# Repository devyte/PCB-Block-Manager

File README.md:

# Block Manager 
### Hardware Files For The Block Manager Board
These are the printed circuit board (PCB) files, CAD files, specification sheets and all technical drawings needed to make the DKblock Block Manager board. There are two boards that make a minimum DK system, a Block Manager PCB and a Pack Supervisor PCB (with software changes to the 20 client version provided). Note that the bill of materials (BOM) and other technical documents can be opened in [OpenOffice](https://www.openoffice.org) format and PCB files are in [EAGLE](https://www.autodesk.com/products/eagle/overview) format but they can also be opened and edited in the open source Kicad program.
One version is provided, that is Rev D which is a fully tested board.

All DKblock software and hardware is released as open source hardware (OSHW) as defined by the OSHWA: https://www.oshwa.org/definition/ and under the JSON license defined at https://www.json.org/license.html

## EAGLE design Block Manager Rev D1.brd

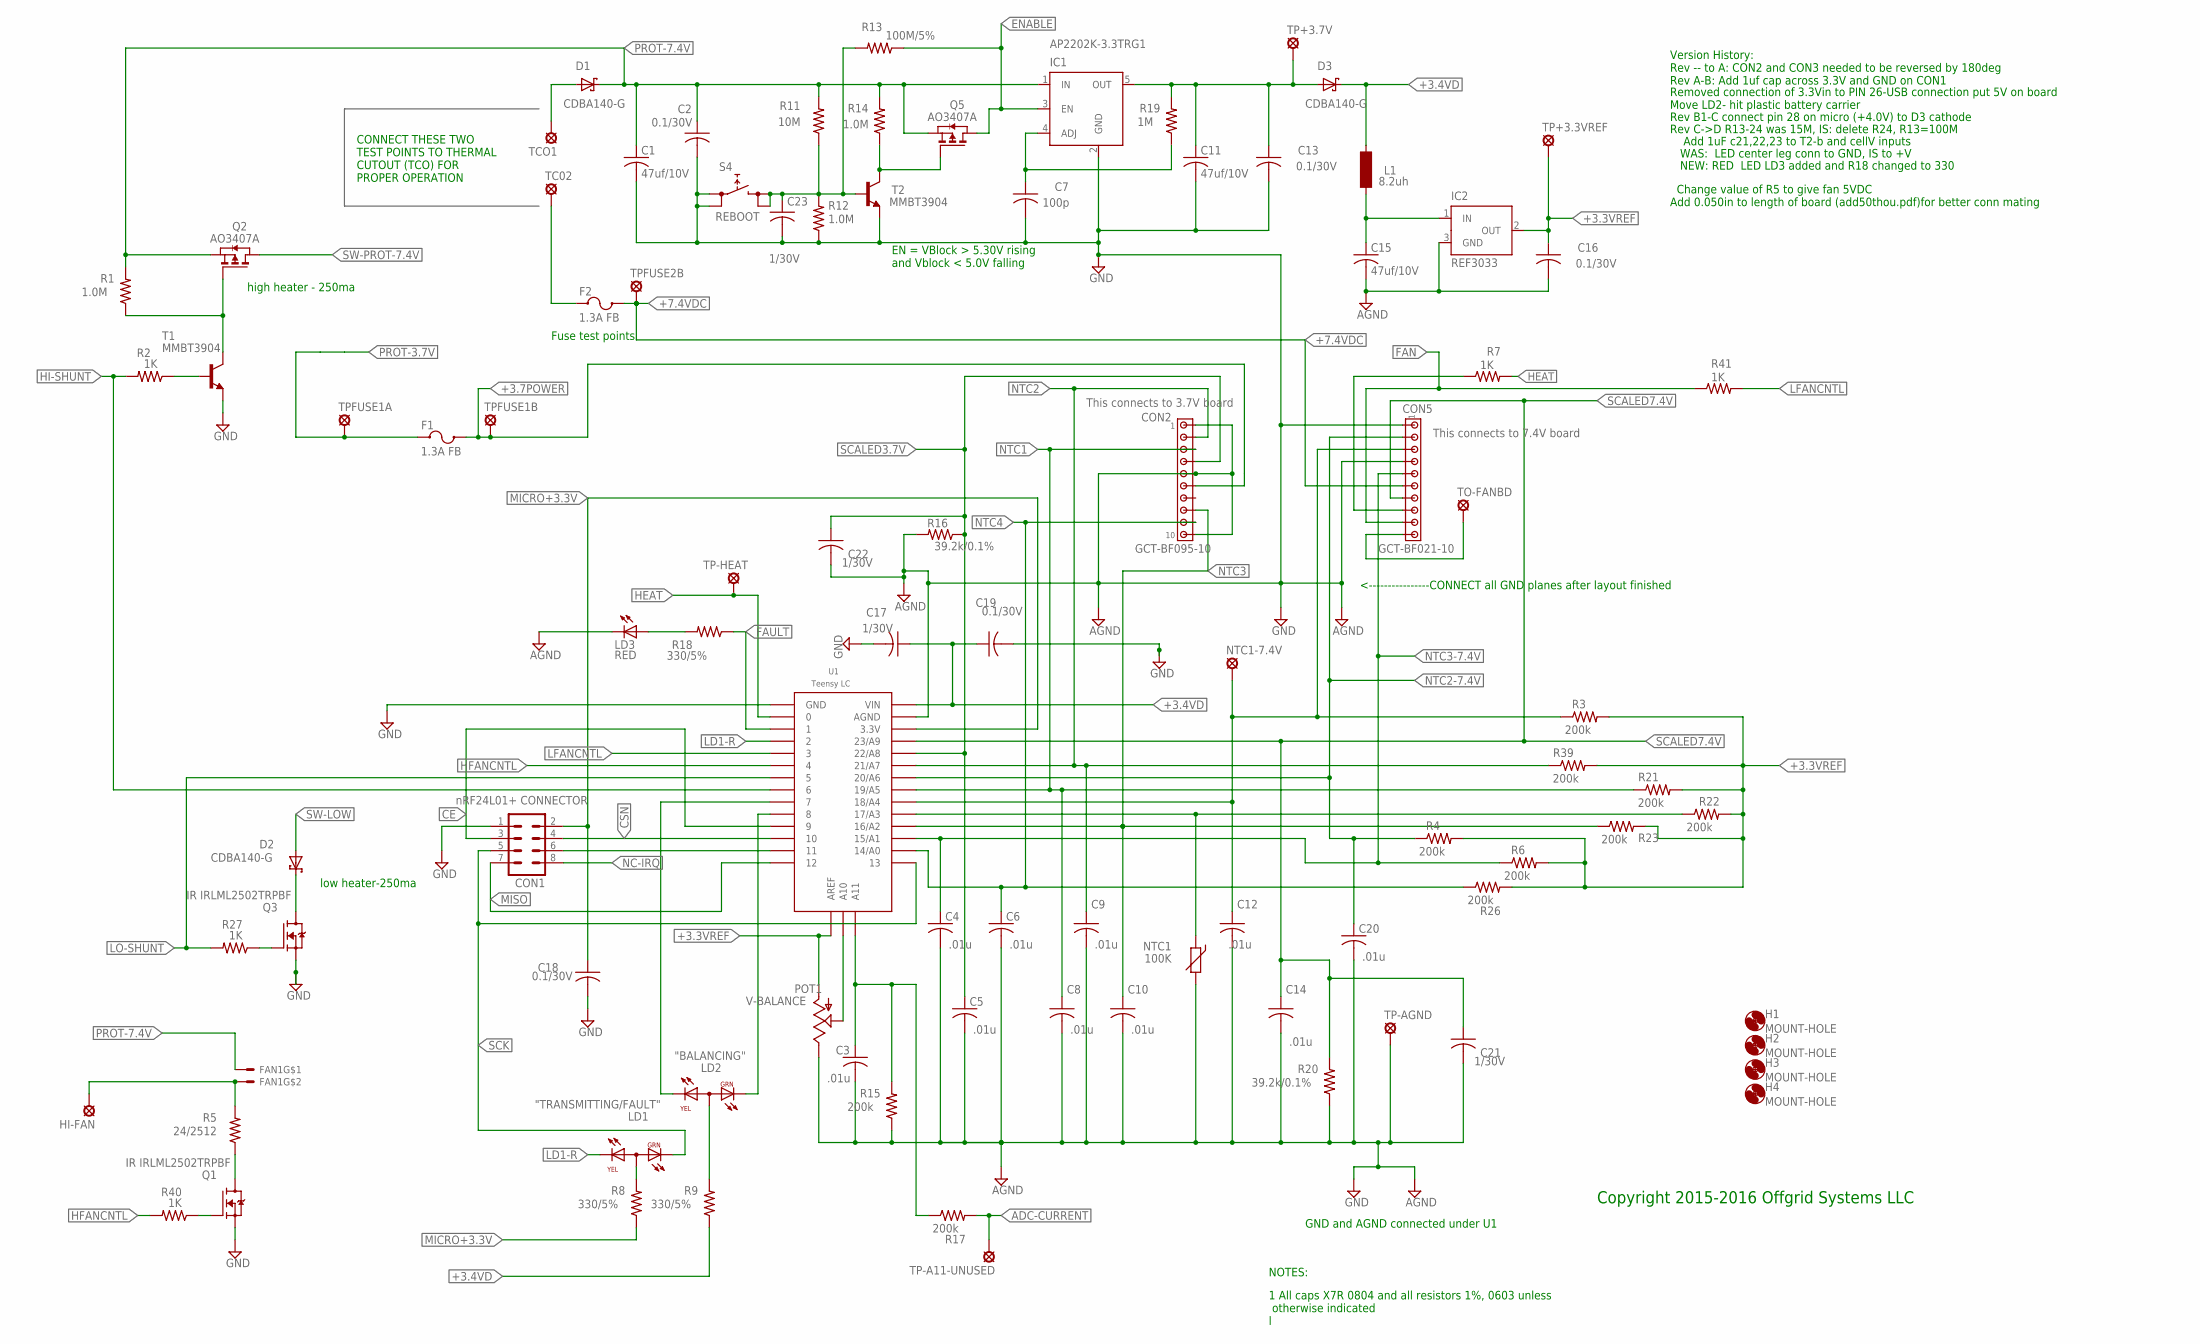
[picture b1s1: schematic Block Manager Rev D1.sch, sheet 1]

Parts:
C1, C11, C15: 47uf/10V; C0805K; MPN Murata GRM21BR61A476ME15L
C2, C13, C16: 0.1/30V; TIMS_INDUCTOR_C0805; MPN Kemet C0805C104K5RACTU
C3, C4, C5, C6, C8, C9, C10, C12, C14, C20: .01u; TIMS_INDUCTOR_C0805; MPN Kemet C0805C103K5RACTU
C7: 100p; TIMS_INDUCTOR_C0805; MPN Kemet C0805C104K5RACTU
C17, C21, C22, C23: 1/30V; TIMS_INDUCTOR_C0805; MPN Kemet C0805C104K5RACTU
C18, C19: 0.1/30V; TIMS_INDUCTOR_C0805; MPN Kemet C0805C103K5RACTU
CON1: nRF24L01+ CONNECTOR; MA04-2; MPN Precidip 803-87-008-10-012101
CON2: GCT-BF095-10; GCT-BF085-10
CON5: GCT-BF021-10
D1, D2, D3: CDBA140-G; DO214AC; MPN comchip CDBA140-G
F1: 1.3A FB; TE-0603SFV125F; MPN TE 0603SFV125F/32-2
F2: 1.3A FB; TE-0603SFV125F; MPN TE 0603SFV125F
FAN1: 30mm fan; 30X30MMFAN; MPN-FAN TBD
H1, H2, H3, H4: MOUNT-HOLE; 2,6
HI-FAN: LSP10
IC1: AP2202K-3.3TRG1; SOT23-5; MPN Diodes AP2202K-3.3TRG1
IC2: REF3033; SOT23; MPN TI REF3033AIDBZR
L1: 8.2uh; SM-1206; MPN Abracon AIML-1206-8R2K-T
LD1: "TRANSMITTING/FAULT"; SUN-XZMDKVG56W; MPN Kingbright APBA3010SYKCGKC-GX
LD2: "BALANCING"; SUN-XZMDKVG56W; MPN Kingbright APBA3010SYKCGKC-GX
LD3: RED; LITEON-LTST-S270KRKT; MPN LITEON-LTST-S270KRKT
NTC1: 100K; 0603; MPN MURATA NCP18WF104J03RB
NTC1-7.4V: LSP10
POT1: V-BALANCE; BOURNS-3361-RA; MPN Bourns 3361S-1-104GLF
Q1, Q3: IRLML2502TRPBF; SOT23; MPN IR IRLML2502TRPBF
Q2: AO3407A; SOT23-BIGPADS; MPN Alpha AO3407A
Q5: AO3407A; SOT23-BIGPADS
R1, R12, R14: 1.0M; R0603; MPN Bourns CR0603-FX-1004ELF
R2, R7, R27, R40, R41: 1K; R0603; MPN Bourns CR0603-FX-1001ELF
R3, R4, R6, R15, R17, R21, R22, R23, R26, R39: 200k; R0603; MPN Bourns CR0603-FX-2003ELF
R5: 24/2512; R2512; MPN Rohm MCR100JZHJ240
R8, R9: 330/5%; R0603; MPN Bourns CR0603-JW-331ELF
R11: 10M; R0603; MPN Bourns CR0603-JW-106ELF
R13: 100M/5%; R0603; MPN Stackpole HMC0603JT100M
R16, R20: 39.2k/0.1%; R0603; MPN Susumu RG1608P-3922-B-T5
R18: 330/5%; R0603; MPN Bourns CR0603-FX-2003ELF
R19: 1M; R0603; MPN Bourns CR0603-FX-1004ELF
S4: REBOOT; PTS645; MPN C&k PTS645SM43SMTR92 LFS
T1, T2: MMBT3904; SOT23-BEC; MPN NXP MMBT3904,215
TC02: SOLPAD1.2MMDRILL; SOLPADWITH1.2MMDRILL
TCO1: SOLPAD1.2MMDRILL; SOLPADWITH1.2MMDRILL
TO-FANBD: LSP10
TP+3.3VREF, TP+3.7V: LSP10
TP-A11-UNUSED: LSP10
TP-AGND: LSP10
TP-HEAT: LSP10
TPFUSE1A, TPFUSE1B, TPFUSE2B: LSP10
U1: Teensy LC; TEENSY_3.0-DIP+ANALOG; MPN OshPark Teensy 3.1

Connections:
4VREFIN: C15.1, IC2.1 (IN), L1.1
+3.3VREF: C16.1, IC2.2 (OUT), POT1.1 (A), R3.2, R4.2, R6.2, R21.2, R22.2, R23.2, R26.2, R39.2, TP+3.3VREF.MP, U1.AREF
+3.4VD: C17.1, C19.1, D3.C, L1.2, R9.1, U1.VIN
+3.7POWER: CON2.P$6 (6), F1.P$2 (2A), TPFUSE1B.MP
+4.5V: C11.1, C13.1, D3.A, IC1.5 (OUT), R19.2, TP+3.7V.MP
+7.4VDC: CON5.P$6 (6), F2.P$2 (2A), TPFUSE2B.MP
ADC-CURRENT: R17.2, TP-A11-UNUSED.MP
ADS: D2.C, Q3.3 (D)
CE: CON1.3, U1.9
CSN: CON1.4, U1.10
ENABLE: IC1.3 (EN), Q5.2 (D), R13.1
FAN: CON5.P$9 (9), R41.1
FAULT: R18.1, U1.1
GND: C1.2, C2.2, C3.2, C4.2, C5.2, C6.2, C7.2, C8.2, C9.2, C10.2, C11.2, C12.2, C13.2, C14.2, C15.2, C16.2, C17.2, C18.2, C19.2, C20.2, C21.2, C22.2, C23.2, CON1.1, CON2.P$1 (1), CON2.P$5 (5), CON2.P$10 (10), CON5.P$1 (1), CON5.P$4 (4), IC1.2 (GND), IC2.3 (GND), LD3.CATHODE (C), NTC1.2, POT1.3 (E), Q1.2 (S), Q3.2 (S), R12.1, R15.1, R16.2, R20.1, S4.1, S4.2, T1.E, T2.E, TP-AGND.MP, U1.AGND, U1.GND
HEAT: R7.2, TP-HEAT.MP, U1.0
HEATER: CON5.P$8 (8), R7.1
HFANCNTL: R40.2, U1.4
HI-SHUNT: R2.2, U1.6
LD1-R: LD1.2-CATH-RED (CR), U1.2
LFANCNTL: R41.2, U1.3
LO-SHUNT: R27.2, U1.5
MICRO+3.3V: C18.1, CON1.2, R8.1, U1.3.3V
MISO: CON1.7, U1.12
MOSI: CON1.6, U1.11
unnamed: LD3.ANODE (A), R18.2
unnamed: D1.A, TCO1.MP
unnamed: NTC1.1, R22.1, U1.17/A3
unnamed: Q2.1 (G), R1.1, T1.C
unnamed: Q1.3 (D), R5.1
unnamed: LD2.3-CATH-GRN (CG), U1.8
unnamed: LD2.2-CATH-RED (CR), U1.7
unnamed: LD1.1-ANODE (A), R8.2
unnamed: F2.P$1 (1A), TC02.MP
unnamed: Q1.1 (G), R40.1
unnamed: Q3.1 (G), R27.1
unnamed: C23.1, R11.1, R12.2, R13.2, S4.3, S4.4, T2.B
unnamed: C7.1, IC1.4 (ADJ), R19.1
unnamed: Q5.1 (G), R14.1, T2.C
unnamed: R2.1, T1.B
unnamed: FAN1.2, HI-FAN.MP, R5.2
NC-IRQ: CON1.8
NTC1: C8.1, CON2.P$3 (3), R21.1, U1.19/A5
NTC1-7.4V: C12.1, CON5.P$3 (3), NTC1-7.4V.MP, R3.1, U1.18/A4
NTC2: C9.1, CON2.P$2 (2), R39.1, U1.21/A7
NTC2-7.4V: C20.1, CON5.P$2 (2), R4.1, U1.20/A6
NTC3: C10.1, CON2.P$8 (8), R23.1, U1.16/A2
NTC3-7.4V: C4.1, CON5.P$5 (5), R6.1, U1.15/A1
NTC4: C6.1, CON2.P$9 (9), R26.1, U1.14/A0
OPENFANBD-PIN: CON5.P$10 (10), TO-FANBD.MP
PROT-3.7V: F1.P$1 (1A), TPFUSE1A.MP; also elsewhere on the board
PROT-7.4V: C1.1, C2.1, D1.C, FAN1.1, IC1.1 (IN), Q2.3 (S), Q5.3 (S), R1.2, R11.2, R14.2
SCALED3.7V: C5.1, C22.1, CON2.P$4 (4), R16.1, U1.22/A8
SCALED7.4V: C14.1, C21.1, CON5.P$7 (7), R20.2, U1.23/A9
SCK: CON1.5, LD1.3-CATH-GRN (CG), U1.13
SW-LOW: D2.A; also elsewhere on the board
SW-PROT-7.4V: Q2.2 (D); also elsewhere on the board
T: LD2.1-ANODE (A), R9.2
UNUSED-ADC: C3.1, R15.2, R17.1, U1.A11
VBALANCE: POT1.2 (S), U1.A10

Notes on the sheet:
Copyright 2015-2016 Offgrid Systems LLC
GND and AGND connected under U1
NOTES:
1 All caps X7R 0804 and all resistors 1%, 0603 unless otherwise indicated l
Version History: Rev -- to A: CON2 and CON3 needed to be reversed by 180deg Rev A-B: Add 1uf cap across 3.3V and GND on CON1
low heater-250ma
Fuse test points
high heater - 250ma
EN = VBlock > 5.30V rising and Vblock < 5.0V falling
This connects to 3.7V board
<----------------CONNECT all GND planes after layout finished
This connects to 7.4V board
Removed connection of 3.3Vin to PIN 26-USB connection put 5V on board Move LD2- hit plastic battery carrier
CONNECT THESE TWO TEST POINTS TO THERMAL CUTOUT (TCO) FOR PROPER OPERATION
Rev B1-C connect pin 28 on micro (+4.0V) to D3 cathode
Rev C->D R13-24 was 15M, IS: delete R24, R13=100M
Add 1uF c21,22,23 to T2-b and cellV inputs
WAS: LED center leg conn to GND, IS to +V
NEW: RED LED LD3 added and R18 changed to 330
Change value of R5 to give fan 5VDC Add 0.050in to length of board (add50thou.pdf)for better conn mating

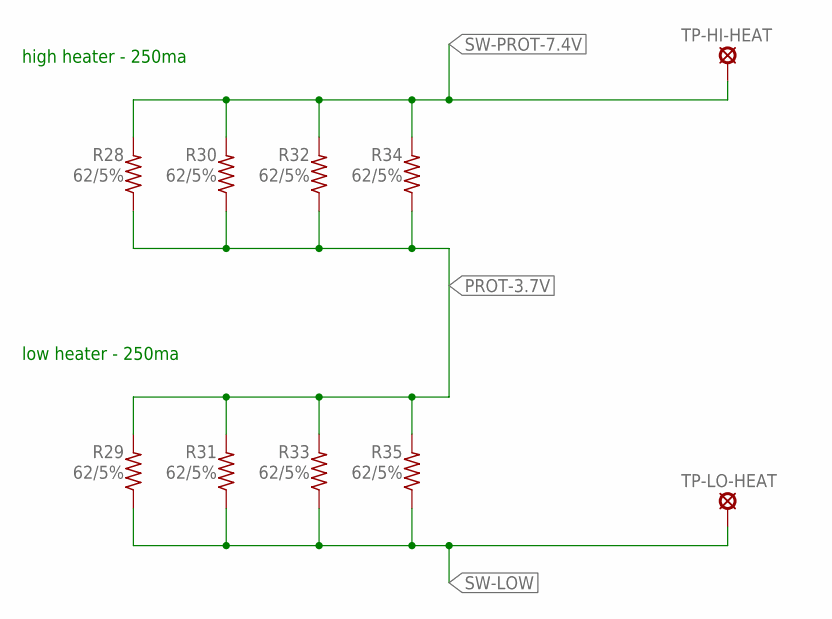
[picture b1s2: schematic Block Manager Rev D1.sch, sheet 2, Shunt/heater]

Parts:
R28, R29, R30, R31, R32, R33, R34, R35: 62/5%; R2512; MPN Rohm MCR100JZHJ620
TP-HI-HEAT: LSP10
TP-LO-HEAT: LSP10

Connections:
PROT-3.7V: R28.1, R29.2, R30.1, R31.2, R32.1, R33.2, R34.1, R35.2; also elsewhere on the board
SW-LOW: R29.1, R31.1, R33.1, R35.1, TP-LO-HEAT.MP; also elsewhere on the board
SW-PROT-7.4V: R28.2, R30.2, R32.2, R34.2, TP-HI-HEAT.MP; also elsewhere on the board

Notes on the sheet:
high heater - 250ma
low heater - 250ma

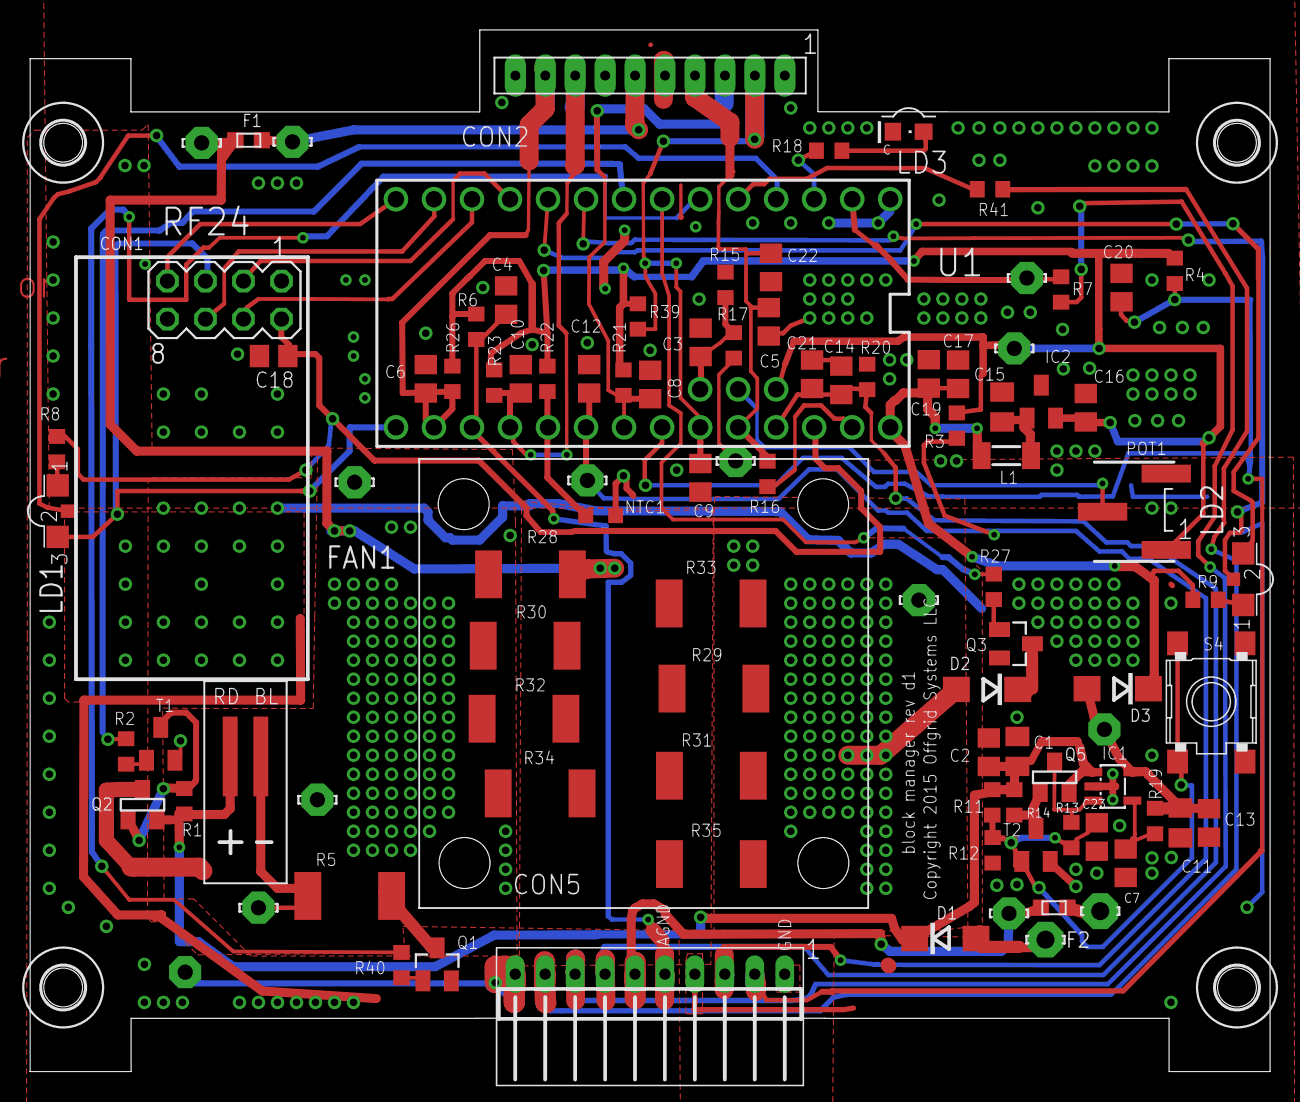
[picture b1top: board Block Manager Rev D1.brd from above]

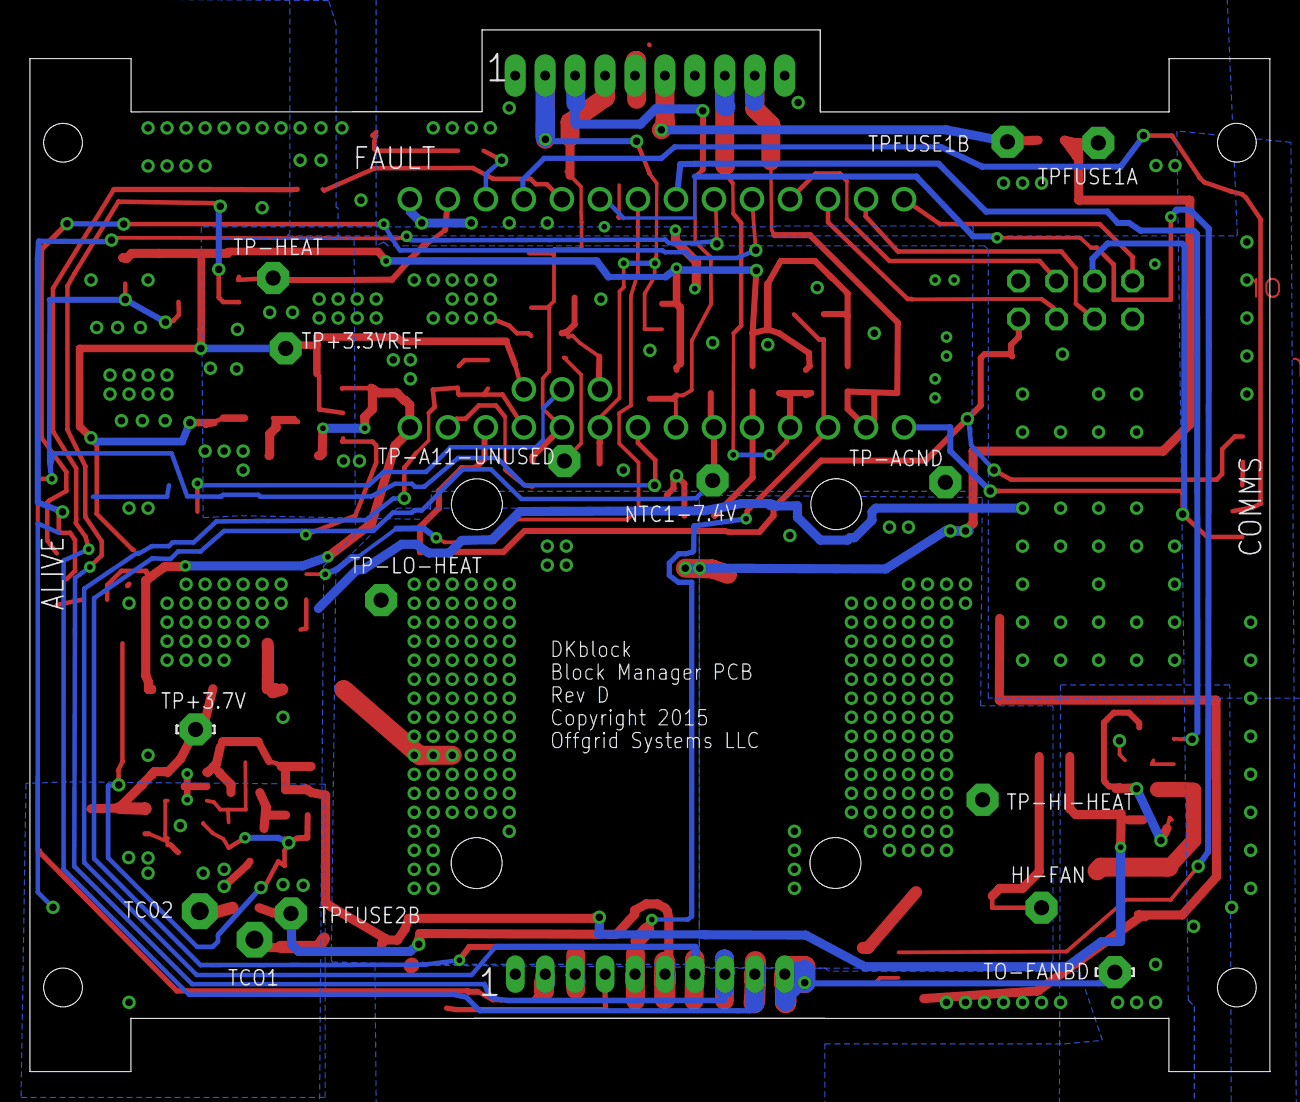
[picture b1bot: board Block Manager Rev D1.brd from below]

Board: 2 copper layers, 82.8 x 69.6 mm, 103 parts (2 on the bottom side), 58 nets.

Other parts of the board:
DRILEGEND: DRILEGEND

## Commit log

2019-11-19 Block Manager document update
2019-11-19 PCB layout in Eagle
2019-11-19 Eagle schematic for Block Manager
2019-11-19 Eagle board layout for Block Manager
2019-11-19 For next board, use to extend board
2019-11-19 Picture of board and functions
2019-11-19 Block manager picture and functions
2019-11-19 add picture of board
2019-11-23 Readme and Image Updates
2020-03-04 Create V2 new radio
2020-03-04 New Sub ghz chip dev tool
2020-03-04 New DK Block Manager chip for faster better comms
2020-03-16 Kicad update

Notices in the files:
Block Manager Rev D1.brd:
Copyright 2015 Offgrid Systems LLC
